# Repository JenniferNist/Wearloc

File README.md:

# Wearloc

* Plan A:
    * Alles auf Edison
* Plan B:
    * Leistungsfähigeren Chip
* Plan C:
    * Daten per W-Lan weitersenden (ESP8266)

* Offene Fragen:
    * Odometry
    * Design
    * Stromversorgung/Verbrauch
    * Sensor Stabilisierung
    * Translation Sensor?
    * 3D vs 2D SLAM

* Zum Angucken:
    * Team Hector Mapping
    * Intel Edison

Treffen: Freitags 10-12  
ROS version: Indigo

Backup raspberry pies von Lukas oder Andre

Verwendbare Laserscanner:  
[RPLIDAR 360° Laser Scanner](http://www.robotshop.com/eu/en/rplidar-360-laser-scanner.html) ([ROS package](http://wiki.ros.org/rplidar))  
[Hokuyo URG-04LX Scanning Laser Rangefinder](http://www.robotshop.com/eu/en/hokuyo-urg-04lx-scanning-laser-rangefinder-eu.html) ([ROS package](http://wiki.ros.org/hokuyo_node))  
  
Nützlich:  
[ROS networking Tutorial](http://nootrix.com/software/ros-networking/)
note: !export ROS_... commands in EVERY terminal window!

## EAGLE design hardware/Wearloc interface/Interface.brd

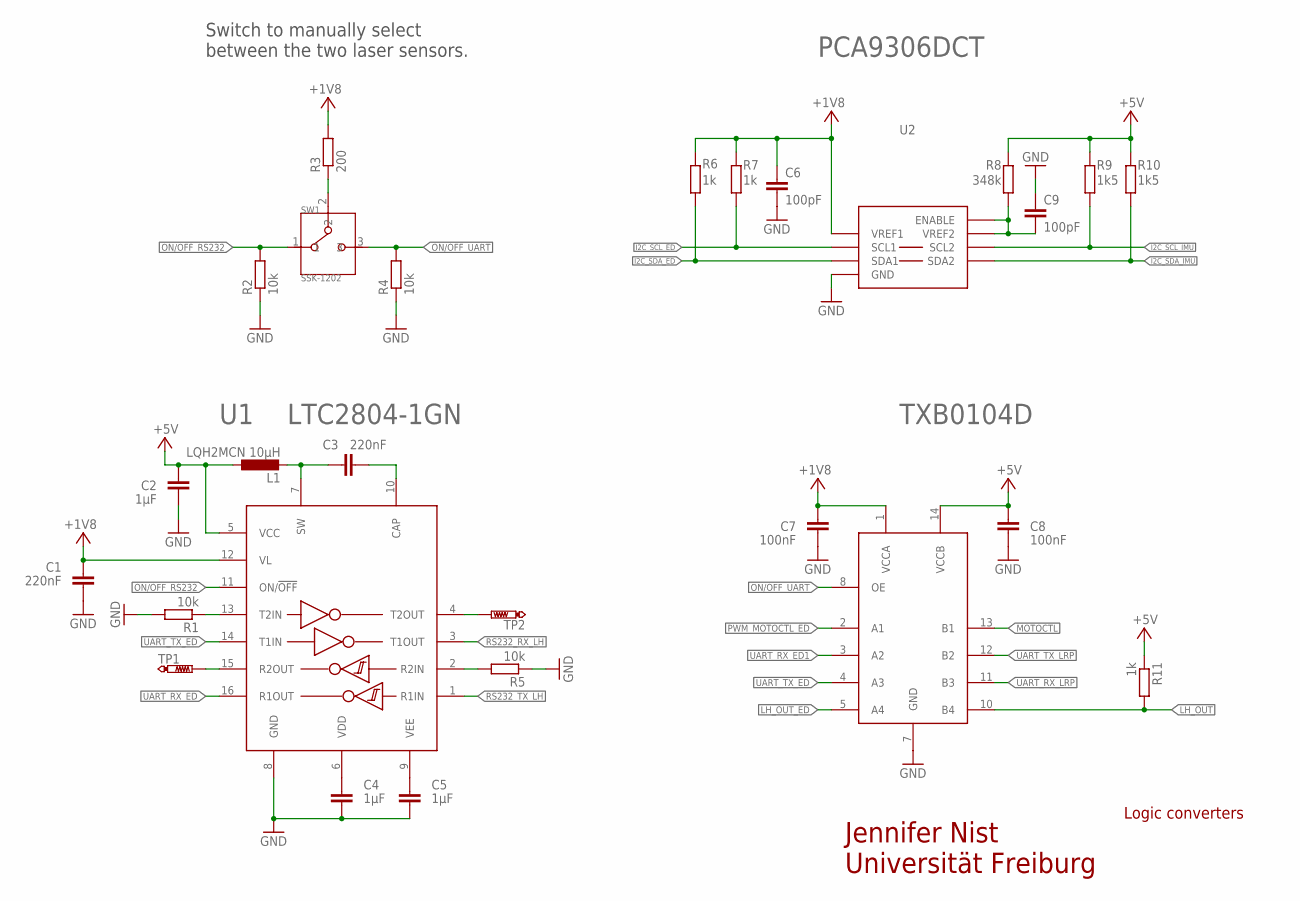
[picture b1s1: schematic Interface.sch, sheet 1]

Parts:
C1, C3: 220nF; C0805K
C2, C4, C5: 1µF; C0805K
C6, C9: 100pF; C0805K
C7, C8: 100nF; C0805K
L1: LQH2MCN 10µH; L0806
R1, R2, R4, R5: 10k; R0805
R3: 200; R0805
R6, R7: 1k; R1206
R8: 348k; R0805
R9, R10: 1k5; R1206
R11: 1k; R0805
SW1: SSK-1202
TP1, TP2: PTR1B1,27; B1,27
U1: LTC2804-1GN; SSOP-16
U2: PCA9306DCT; SSOP-8
U3: TXB0104D; SOIC-14

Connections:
+1V8: C1.2, C6.2, C7.1, R3.2, R6.1, R7.1, U1.12 (VL), U2.2 (VREF1), U3.1 (VCCA); also elsewhere on the board
+5V: C2.2, C8.1, L1.1, R8.2, R9.2, R10.2, R11.1, U1.5 (VCC), U3.14 (VCCB); also elsewhere on the board
GND: C1.1, C2.1, C4.2, C5.2, C6.1, C7.2, C8.2, C9.2, R1.2, R2.1, R4.1, R5.1, U1.8 (GND), U2.1 (GND), U3.7 (GND); also elsewhere on the board
I2C_SCL_ED: R7.2, U2.3 (SCL1); also elsewhere on the board
I2C_SCL_IMU: R9.1, U2.6 (SCL2); also elsewhere on the board
I2C_SDA_ED: R6.2, U2.4 (SDA1); also elsewhere on the board
I2C_SDA_IMU: R10.1, U2.5 (SDA2); also elsewhere on the board
LH_OUT: R11.2, U3.10 (B4); also elsewhere on the board
LH_OUT_ED: U3.5 (A4); also elsewhere on the board
MOTOCTL: U3.13 (B1); also elsewhere on the board
unnamed: R3.1, SW1.2
unnamed: C3.1, L1.2, U1.7 (SW)
unnamed: C9.1, R8.1, U2.7 (VREF2), U2.8 (ENABLE)
unnamed: C3.2, U1.10 (CAP)
unnamed: R1.1, U1.13 (T2IN)
unnamed: R5.2, U1.2 (R2IN)
unnamed: TP2.TP, U1.4 (T2OUT)
unnamed: TP1.TP, U1.15 (R2OUT)
ON/OFF_RS232: R2.2, SW1.1, U1.11 (ON/!OFF)
ON/OFF_UART: R4.2, SW1.3, U3.8 (OE)
PWM_MOTOCTL_ED: U3.2 (A1); also elsewhere on the board
RS232_RX_LH: U1.3 (T1OUT); also elsewhere on the board
RS232_TX_LH: U1.1 (R1IN); also elsewhere on the board
UART_RX_ED: U1.16 (R1OUT); also elsewhere on the board
UART_RX_ED1: U3.3 (A2); also elsewhere on the board
UART_RX_LRP: U3.11 (B3); also elsewhere on the board
UART_TX_ED: U1.14 (T1IN), U3.4 (A3); also elsewhere on the board
UART_TX_LRP: U3.12 (B2); also elsewhere on the board
VDD: C4.1, U1.6 (VDD)
VEE: C5.1, U1.9 (VEE)

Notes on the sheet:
Jennifer Nist Universität Freiburg
Logic converters
Switch to manually select between the two laser sensors.

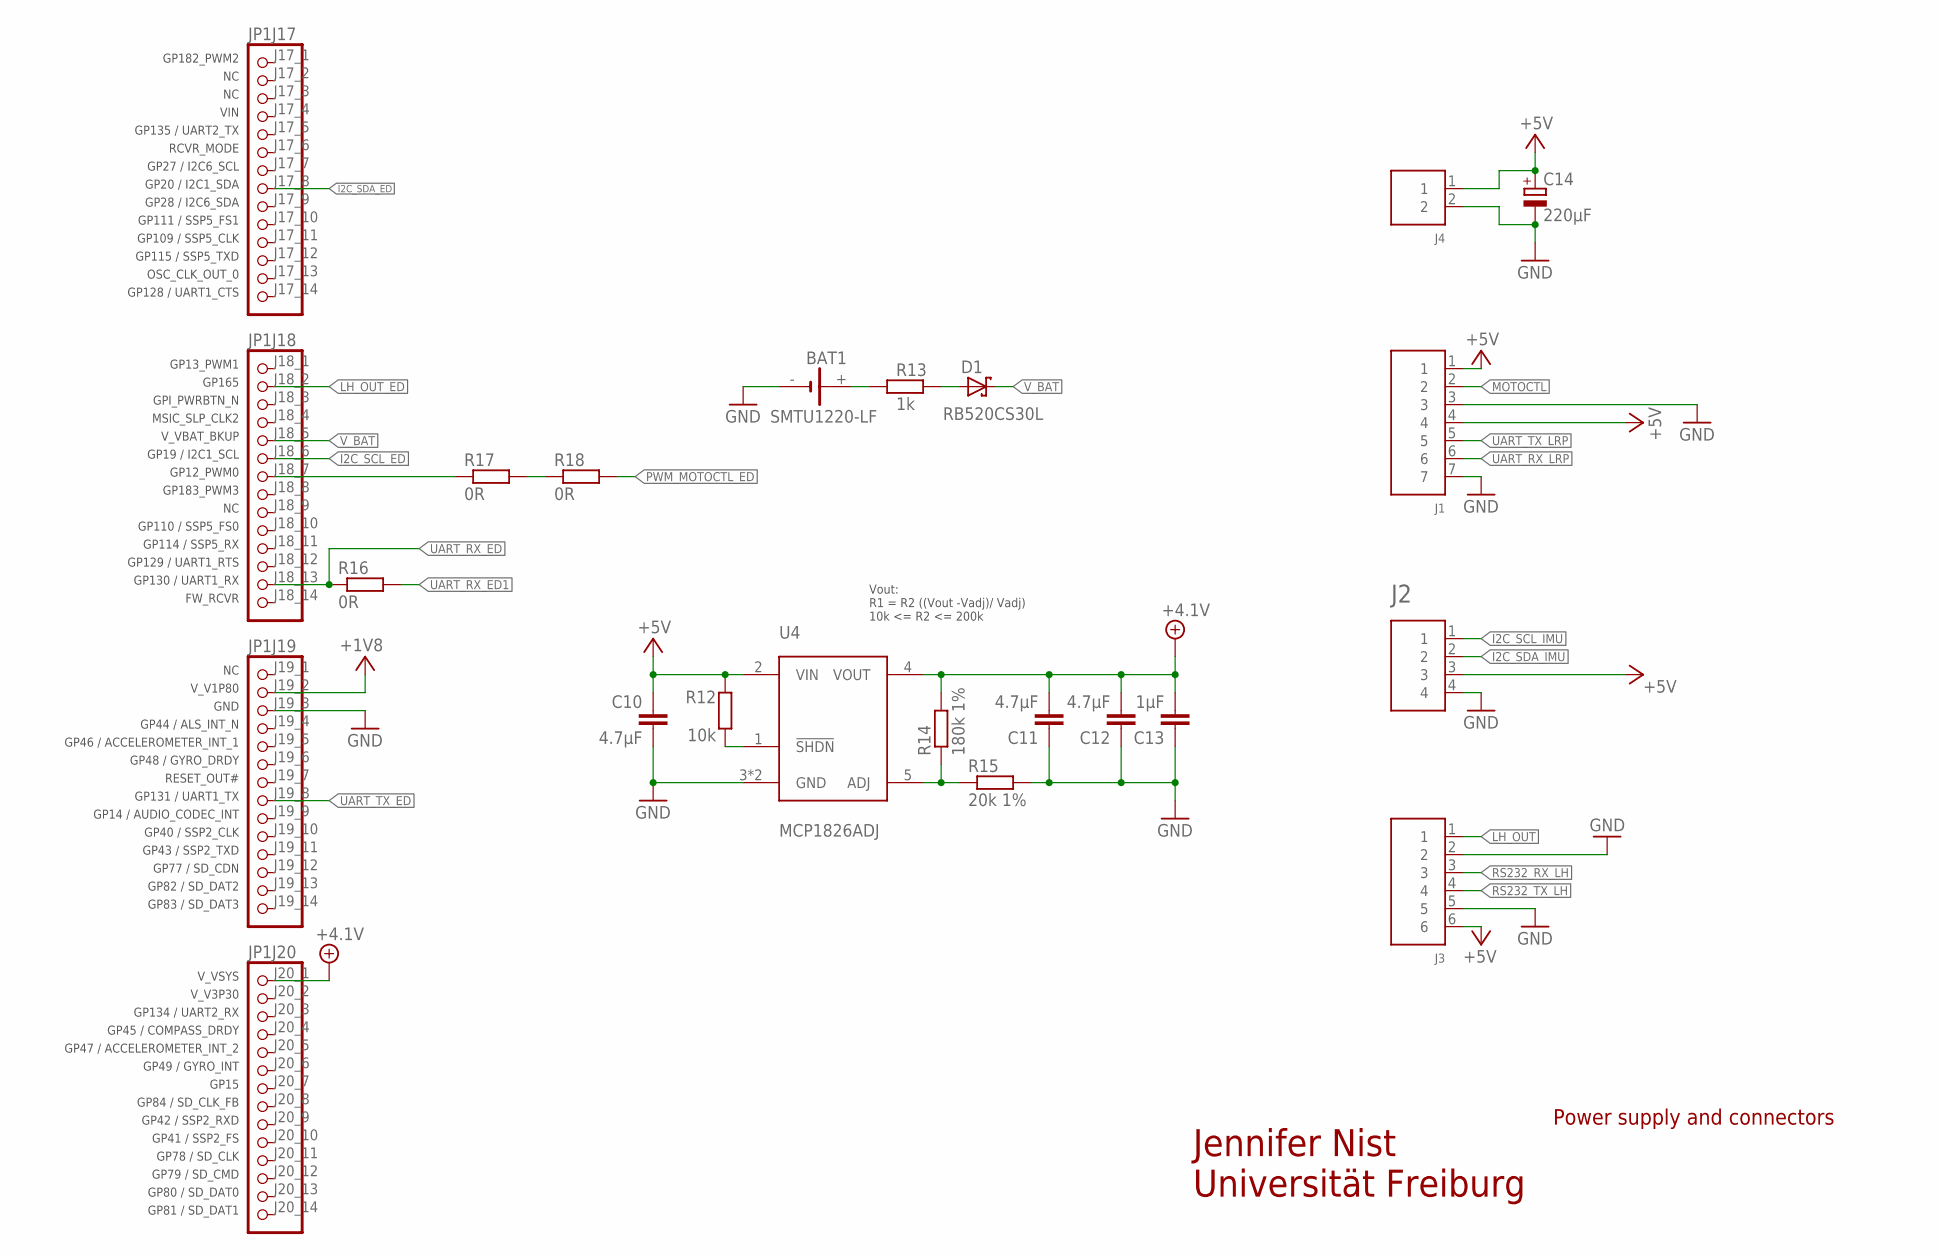
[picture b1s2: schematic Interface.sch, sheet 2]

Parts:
BAT1: SMTU1220-LF
C10, C11, C12: 4.7µF; C0805K
C13: 1µF; C0805K
C14: 220µF; E3,5-8
D1: RB520CS30L; SOD882
J1: S7B-XH-A90°; S7B-XH-A
J2: S4B-XH-A90°; S4B-XH-A
J3: S6B-XH-A90°; S6B-XH-A
J4: S2B-XH-A90°; S2B-XH-A
JP1: edison; 1X14
R12: 10k; R0805
R13: 1k; R0805
R14: 180k 1%; R0805
R15: 20k 1%; R0805
R16, R17, R18: 0R; R1206
U4: MCP1826ADJ; SOT-223-5

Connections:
+1V8: JP1.J19_2 (2); also elsewhere on the board
+4.1V: C11.2, C12.2, C13.2, JP1.J20_1 (1), R14.2, U4.4 (VOUT)
+5V: C10.1, C14.+, J1.1, J1.4, J2.3, J3.6, J4.1, R12.2, U4.2 (VIN); also elsewhere on the board
GND: BAT1.-, C10.2, C11.1, C12.1, C13.1, C14.-, J1.3, J1.7, J2.4, J3.2, J3.5, J4.2, JP1.J19_3 (3), R15.2, U4.3 (GND), U4.TAB (GND); also elsewhere on the board
I2C_SCL_ED: JP1.J18_6 (6); also elsewhere on the board
I2C_SCL_IMU: J2.1; also elsewhere on the board
I2C_SDA_ED: JP1.J17_8 (8); also elsewhere on the board
I2C_SDA_IMU: J2.2; also elsewhere on the board
LH_OUT: J3.1; also elsewhere on the board
LH_OUT_ED: JP1.J18_2 (2); also elsewhere on the board
MOTOCTL: J1.2; also elsewhere on the board
unnamed: BAT1.+, R13.1
unnamed: R12.1, U4.1 (!SHDN)
unnamed: R14.1, R15.1, U4.5 (ADJ)
unnamed: D1.A, R13.2
unnamed: JP1.J18_7 (7), R17.1
unnamed: R17.2, R18.1
PWM_MOTOCTL_ED: R18.2; also elsewhere on the board
RS232_RX_LH: J3.3; also elsewhere on the board
RS232_TX_LH: J3.4; also elsewhere on the board
UART_RX_ED: JP1.J18_13 (13), R16.1; also elsewhere on the board
UART_RX_ED1: R16.2; also elsewhere on the board
UART_RX_LRP: J1.6; also elsewhere on the board
UART_TX_ED: JP1.J19_8 (8); also elsewhere on the board
UART_TX_LRP: J1.5; also elsewhere on the board
V_BAT: D1.C, JP1.J18_5 (5)

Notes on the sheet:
Jennifer Nist Universität Freiburg
Power supply and connectors
Vout: R1 = R2 ((Vout -Vadj)/ Vadj) 10k <= R2 <= 200k

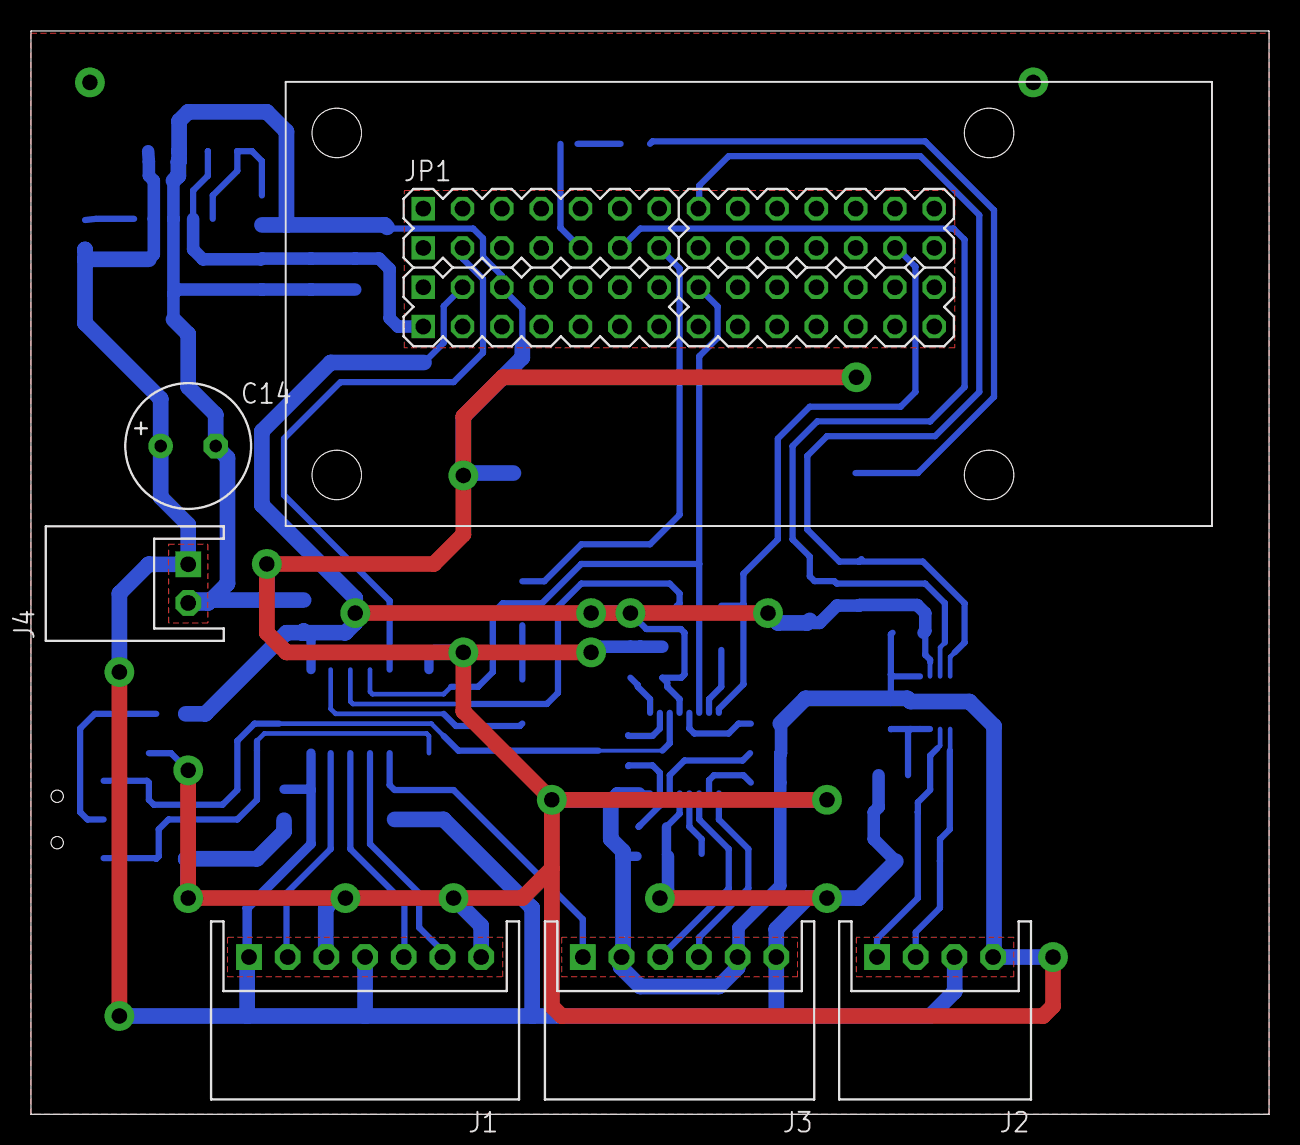
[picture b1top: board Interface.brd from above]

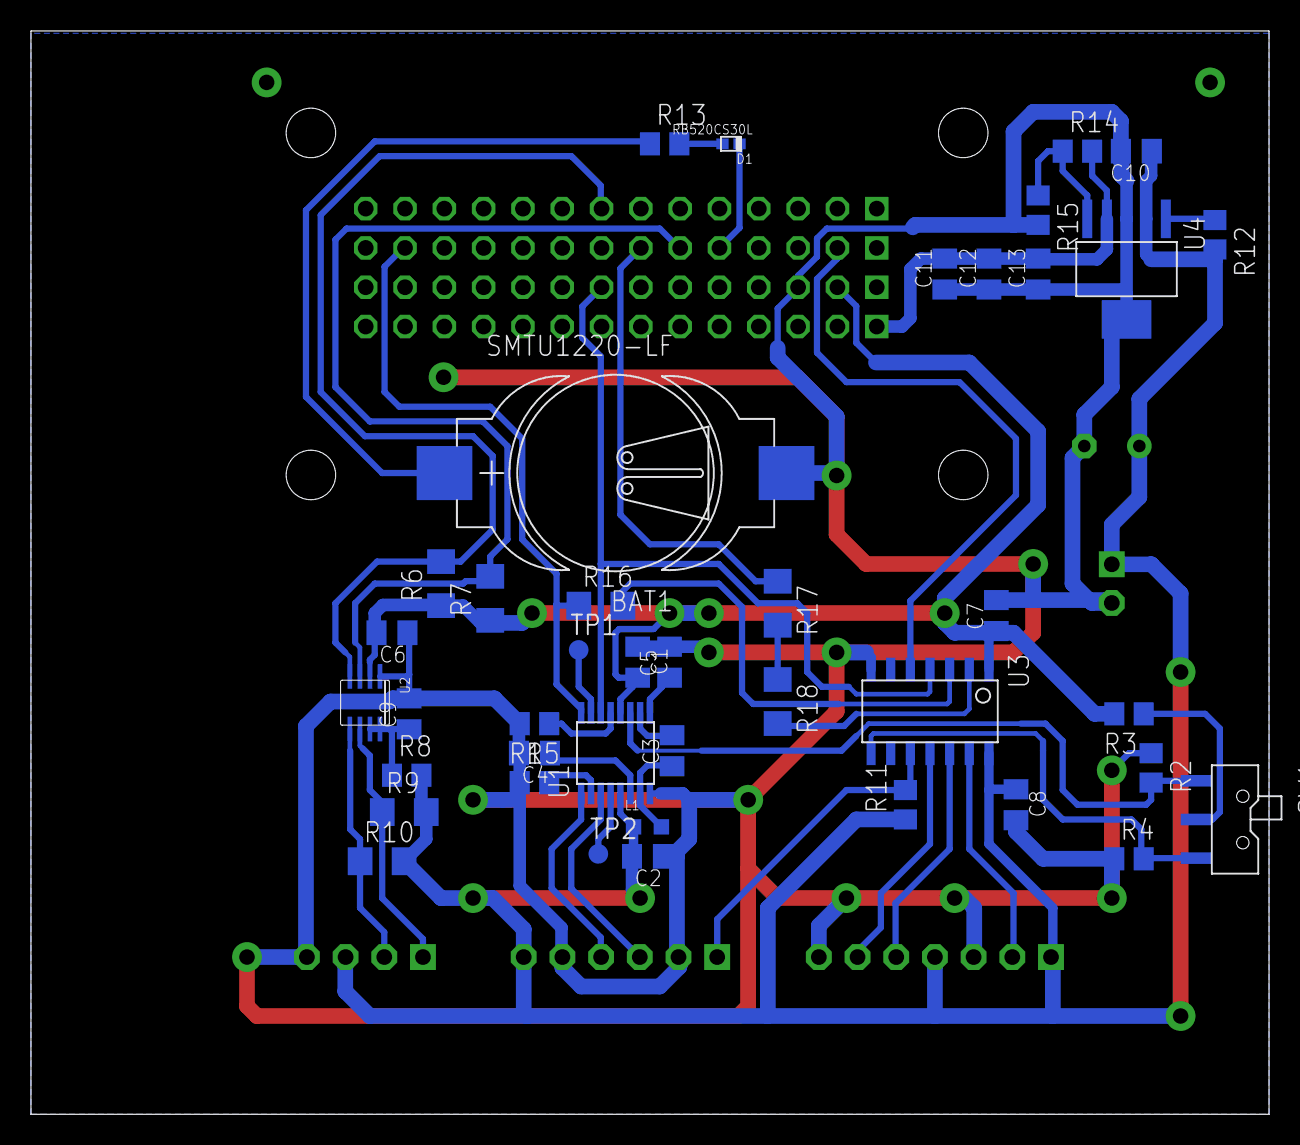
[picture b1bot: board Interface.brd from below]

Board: 2 copper layers, 80.0 x 70.0 mm, 47 parts (41 on the bottom side), 38 nets.

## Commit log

2016-04-27 test
2016-04-27 removed test files
2016-04-27 Treffen 27.4
2016-04-27 Minor
2016-04-28 typo fix
2016-04-29 first draft presentation
2016-04-29 Laserscanner
2016-04-29 Lukas ist nicht lustig
2016-05-04 final presentation
2016-05-04 Launch files for static SLAM with RPLIDAR
2016-05-04 added location info for .launch files
2016-05-04 network tutorial info
2016-05-04 Added Cheatsheet for ROS
2016-05-06 documatation for the different hardware devices and helps
2016-05-06 Library for Gyro server
2016-05-06 Added src folder for code
2016-05-06 now with src fodler
2016-05-09 Datenblatt hinzugefügt
2016-05-09 started developing interface board
2016-05-09 added next eagle device to library
2016-05-09 added eagle library for level shifter
2016-05-10 started creating interface schematic
2016-05-10 Developed interface schematic and its devices.
2016-05-11 interface board work in progress
2016-05-11 working ros structure
2016-05-12 worked on schematic
2016-05-13 small changes
2016-05-13 collected some documentation
2016-05-13 added help for configuring home and university wifi for edison
2016-05-15 worked on interface schematic
2016-05-17 finished first prototype interface schematic
2016-05-18 First routing attempt.
2016-05-20 almost finished schematic
2016-05-20 small changes in board layout
2016-05-25 Added documentation for 2nd IMU-board.
2016-06-01 clean up commit
2016-06-01 Added libraries for different IMUs.
2016-06-06 added midterm presentation source + pdf
2016-06-06 minor changes on midterm presentation
2016-06-06 moved initial presentation, removed binary files
2016-06-08 minor changes in midterm presentation
2016-06-14 Added file with desccription of the currend state of intel edison. Please use it to get familiar with intel edison, its usage and implemented software.
2016-06-15 Added examples and more hints.
2016-06-15 solved problem
2016-06-15 next changes
2016-06-27 Added the first draft of the poster
2016-07-06 First draft of our report
2016-07-12 Minor changes to the report
2016-07-13 two experiment pics
2016-07-13 Added Poster with more images
2016-07-14 final version of poster
2016-07-14 Fixed typo
2016-07-18 cur slam version
2016-07-18 Anleitung für Backup and Restore für ubilinux erstellt.
2016-07-19 Minor changes.
2016-07-21 Minor changes
2016-08-15 Tried to write small Software part. Needs elaboration
2016-08-18 revised the report
2016-08-18 minor text fixes
2016-08-19 another revision of the report
2016-08-19 Lulu
2016-08-25 Added Bibliography
2016-08-26 trying to fix my git connection
2016-09-15 Fixed Wearbale to Wearable
